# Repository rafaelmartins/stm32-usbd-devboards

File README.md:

<!-- github-to-forgejo:notice:start -->
> [!IMPORTANT]
> Development has moved to [https://git.rafaelmartins.com/rafaelmartins/stm32-usbd-devboards](https://git.rafaelmartins.com/rafaelmartins/stm32-usbd-devboards). Please check [https://git.rafaelmartins.com/](https://git.rafaelmartins.com/) for details on how to contribute.
<!-- github-to-forgejo:notice:end -->

# stm32-usbd-devboards

Breadboard-friendly development boards with dedicated USB device connectivity for STM32 microcontrollers.

For documentation please visit: https://rafaelmartins.com/p/stm32-usbd-devboards/

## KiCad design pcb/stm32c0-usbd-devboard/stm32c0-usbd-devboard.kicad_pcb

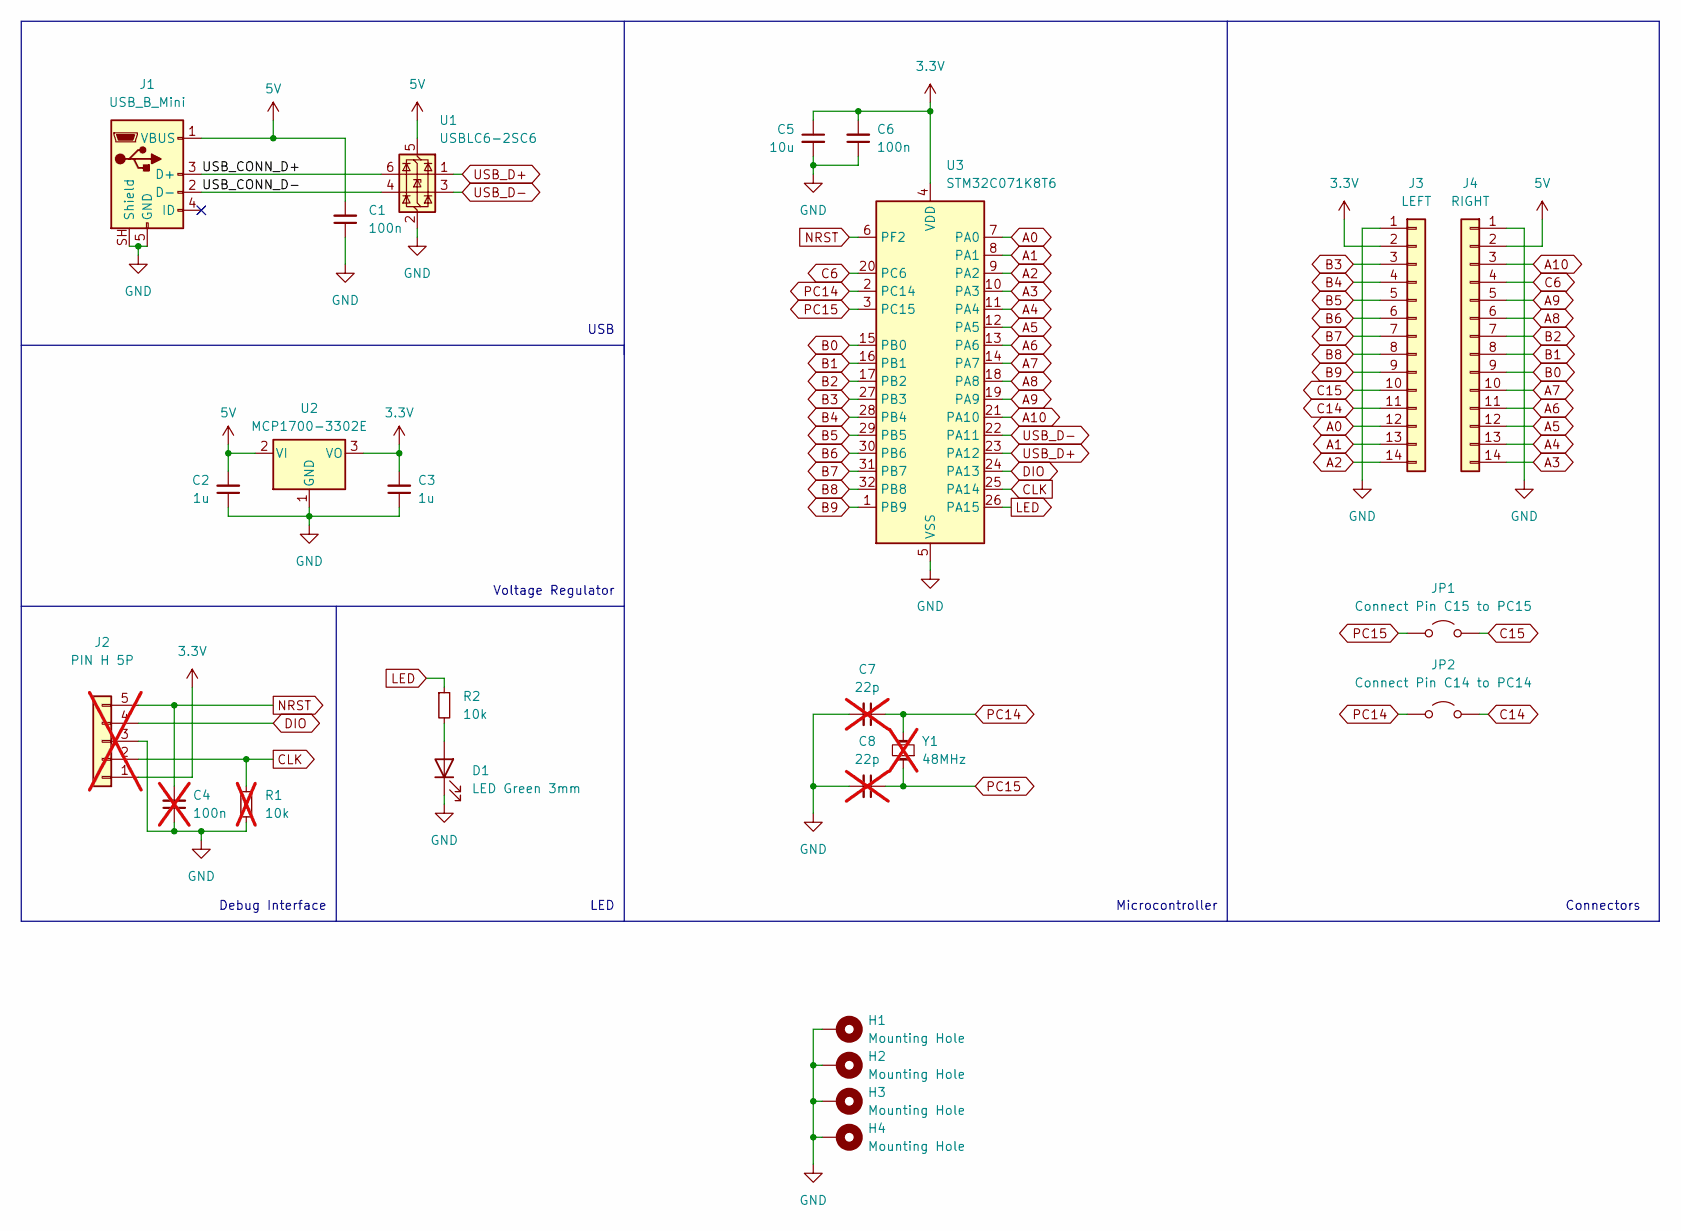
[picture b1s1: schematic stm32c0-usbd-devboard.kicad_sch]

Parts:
C1, C6: 100n; C_TDK_FA28; MPN FA28X7R1H104KNU06
C2, C3: 1u; C_TDK_FA28; MPN FA28X7R1E105KRU06
C4: 100n; C_TDK_FA28; MPN FA28X7R1H104KNU06; not fitted
C5: 10u; C_TDK_FA26; MPN FA26X7R1E106KRU06
C7, C8: 22p; C_Disc_D3.8mm_W2.6mm_P2.50mm; MPN FA28X7R1H104KNU06; not fitted
D1: LED Green 3mm; LED_D3.0mm_Horizontal_O1.27mm_Z2.0mm; MPN OVLBG4C7
H1, H2, H3, H4: Mounting Hole; MountingHole_2.2mm_M2_Pad_Via
J1: USB_B_Mini; USB_Mini-B_PTH; MPN GMSB0522132EU
J2: PIN H 5P; PinHeader_Bootloader_SWD_1x05_P2.54mm_Vertical; not fitted
J3: LEFT; PinHeader_DevBoard_Left_Connector_1x14_P2.54mm_Vertical
J4: RIGHT; PinHeader_DevBoard_Right_Connector_1x14_P2.54mm_Vertical
JP1: Connect Pin C15 to PC15; SolderJumper-2_P1.3mm_Open_TrianglePad1.0x1.5mm
JP2: Connect Pin C14 to PC14; SolderJumper-2_P1.3mm_Open_TrianglePad1.0x1.5mm
R1: 10k; R_YAGEO_MFR-25FTE52_Horizontal; MPN MFR-25FTE52-10K; not fitted
R2: 10k; R_YAGEO_MFR-25FTE52_Horizontal; MPN MFR-25FTE52-10K
U1: USBLC6-2SC6; SOT-23-6; MPN USBLC6-2SC6
U2: MCP1700-3302E; TO-92_Inline_Wide; MPN MCP1700-3302E/TO
U3: STM32C071K8T6; LQFP-32_7x7mm_P0.8mm
Y1: 48MHz; Crystal_HC49-4H_Vertical; not fitted

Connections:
3.3V: C3.2, C5.1, C6.2, J2.1, J3.2, U2.3 (VO), U3.4 (VDD)
5V: C1.2, C2.2, J1.1 (VBUS), J4.2, U1.5 (VBUS), U2.2 (VI)
/USB_CONN_D+: J1.3 (D+), U1.6 (I/O1)
/USB_CONN_D-: J1.2 (D-), U1.4 (I/O2)
A0: J3.12, U3.7 (PA0)
A1: J3.13, U3.8 (PA1)
A2: J3.14, U3.9 (PA2)
A3: J4.14, U3.10 (PA3)
A4: J4.13, U3.11 (PA4)
A5: J4.12, U3.12 (PA5)
A6: J4.11, U3.13 (PA6)
A7: J4.10, U3.14 (PA7)
A8: J4.6, U3.18 (PA8)
A9: J4.5, U3.19 (PA9)
A10: J4.3, U3.21 (PA10)
B0: J4.9, U3.15 (PB0)
B1: J4.8, U3.16 (PB1)
B2: J4.7, U3.17 (PB2)
B3: J3.3, U3.27 (PB3)
B4: J3.4, U3.28 (PB4)
B5: J3.5, U3.29 (PB5)
B6: J3.6, U3.30 (PB6)
B7: J3.7, U3.31 (PB7)
B8: J3.8, U3.32 (PB8)
B9: J3.9, U3.1 (PB9)
C6: J4.4, U3.20 (PC6)
C14: J3.11, JP2.1 (A)
C15: J3.10, JP1.1 (A)
CLK: J2.2, R1.1, U3.25 (PA14)
DIO: J2.4, U3.24 (PA13)
GND: C1.1, C2.1, C3.1, C4.1, C5.2, C6.1, C7.2, C8.2, D1.1 (K), H1.1 (1_1), H2.1 (1_1), H3.1 (1_1), H4.1 (1_1), J1.5 (GND), J1.SH (Shield), J2.3, J3.1, J4.1, R1.2, U1.2 (GND), U2.1 (GND), U3.5 (VSS)
LED: R2.1, U3.26 (PA15)
NRST: C4.2, J2.5, U3.6 (PF2)
unnamed: D1.2 (A), R2.2
PC14: C7.1, JP2.2 (B), U3.2 (PC14), Y1.2
PC15: C8.1, JP1.2 (B), U3.3 (PC15), Y1.1
USB_D+: U1.1 (I/O1), U3.23 (PA12)
USB_D-: U1.3 (I/O2), U3.22 (PA11)

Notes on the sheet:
Debug Interface
LED
Microcontroller
Connectors
Voltage Regulator
USB

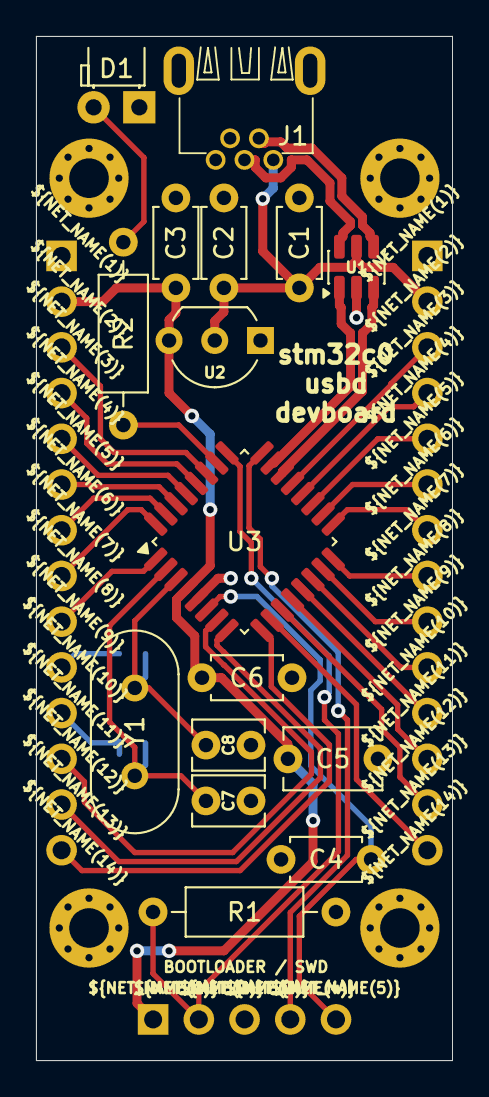
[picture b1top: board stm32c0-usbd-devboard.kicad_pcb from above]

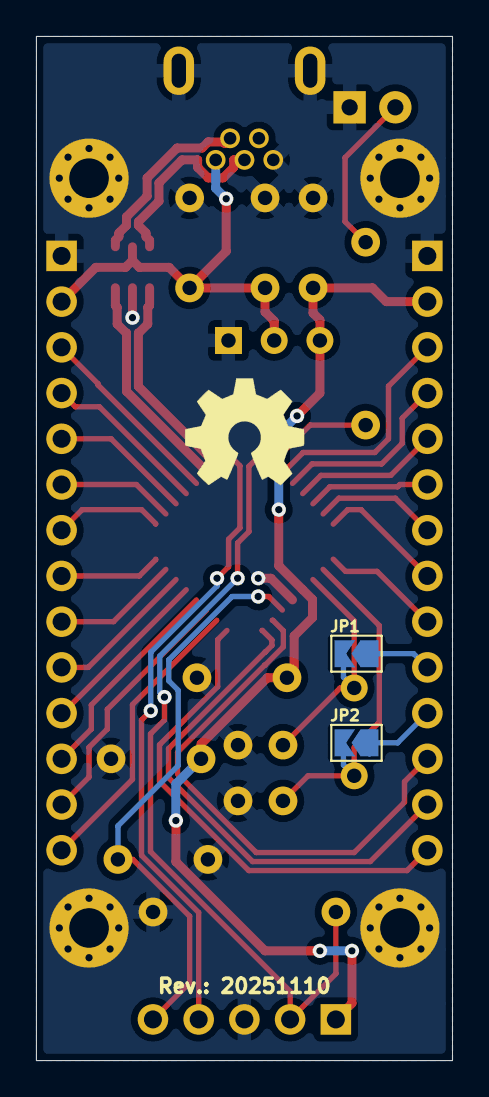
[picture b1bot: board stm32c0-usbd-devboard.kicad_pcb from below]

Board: 2 copper layers, 23.1 x 56.9 mm, 25 parts (4 on the bottom side), 38 nets.

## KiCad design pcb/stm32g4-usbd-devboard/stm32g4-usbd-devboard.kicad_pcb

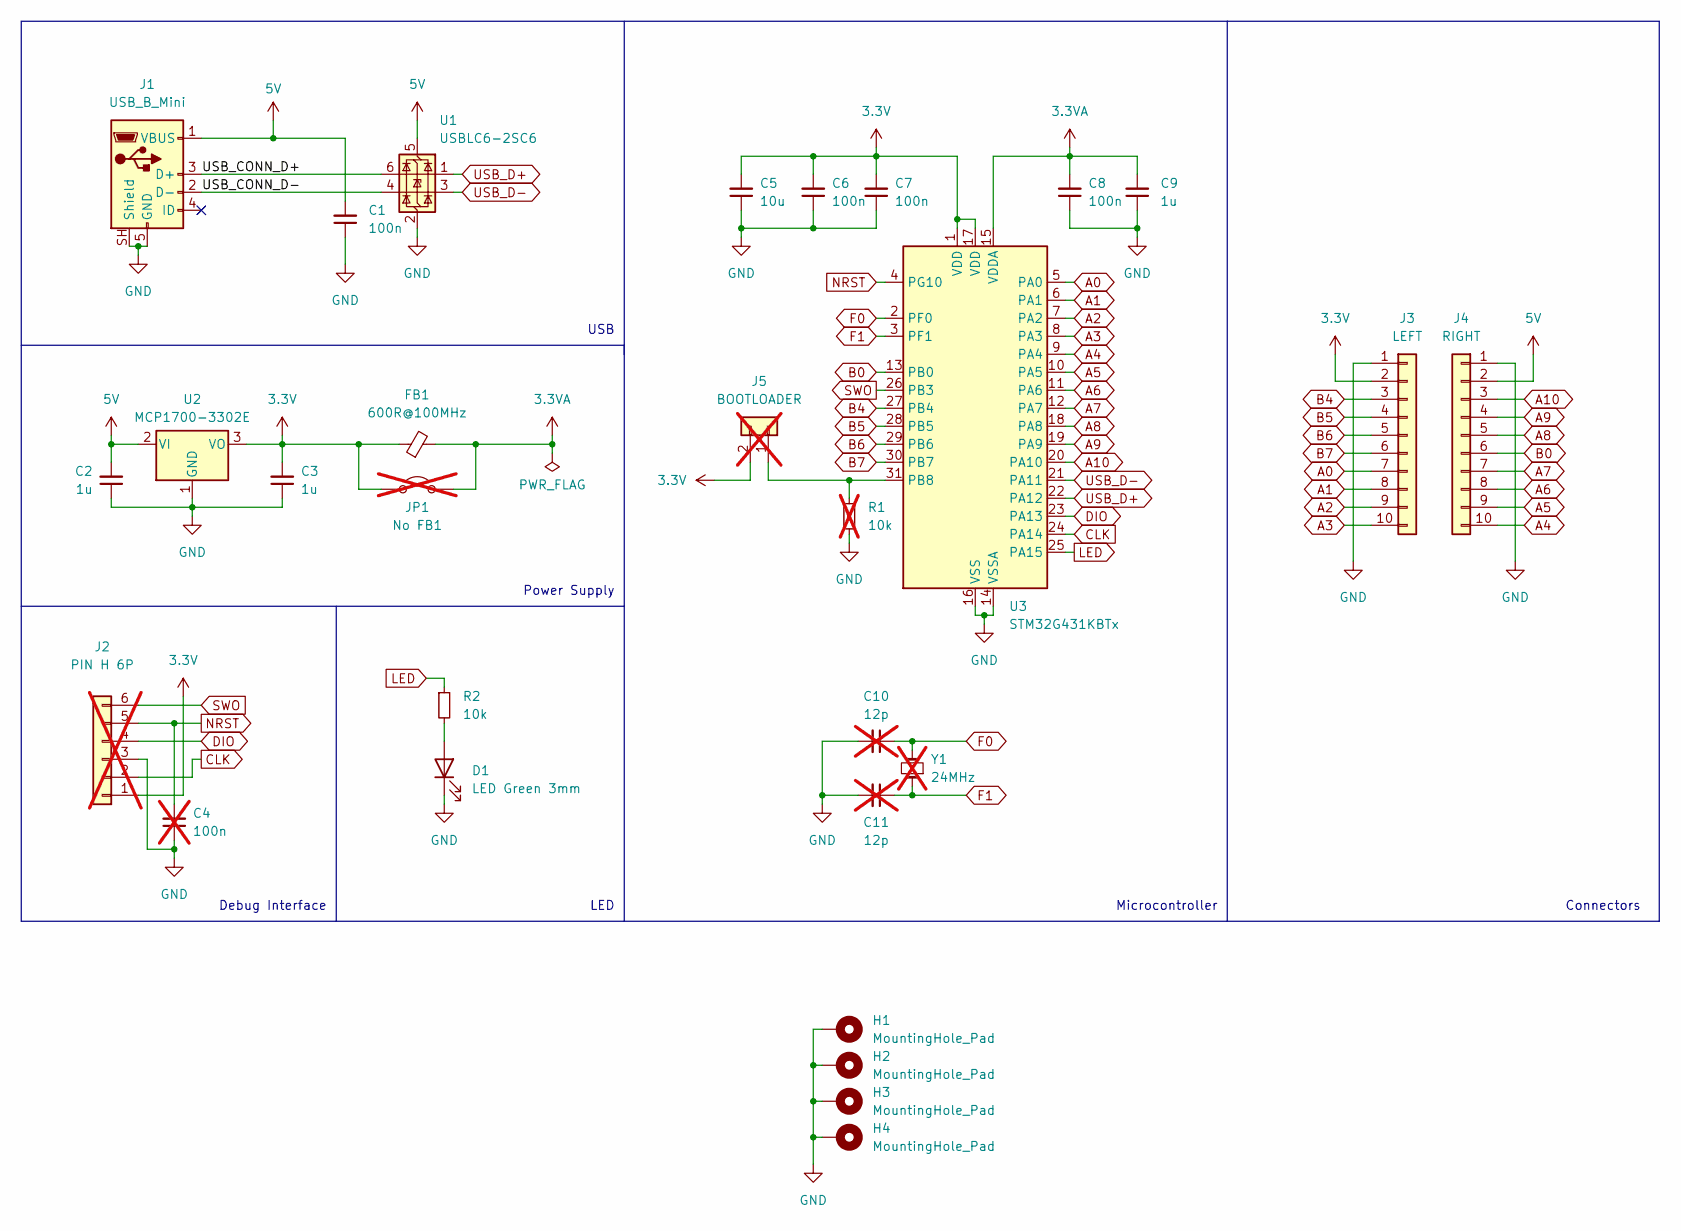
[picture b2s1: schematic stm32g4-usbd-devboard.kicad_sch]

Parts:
C1, C6, C7, C8: 100n; C_TDK_FA28; MPN FA28X7R1H104KNU06
C2, C3: 1u; C_TDK_FA28; MPN FA28X7R1E105KRU06
C4: 100n; C_TDK_FA28; MPN FA28X7R1H104KNU06; not fitted
C5: 10u; C_TDK_FA26; MPN FA26X7R1E106KRU06
C9: 1u; C_TDK_FA28; MPN FA28X7R1H104KNU06
C10, C11: 12p; C_Disc_D3.8mm_W2.6mm_P2.50mm; MPN FA28X7R1E105KRU06; not fitted
D1: LED Green 3mm; LED_D3.0mm_Horizontal_O1.27mm_Z2.0mm; MPN OVLBG4C7
FB1: 600R@100MHz; L_0603_1608Metric_Pad1.05x0.95mm_HandSolder
H1, H2, H3, H4: MountingHole_Pad; MountingHole_2.2mm_M2_Pad_Via
J1: USB_B_Mini; USB_Mini-B_PTH; MPN GMSB0522132EU
J2: PIN H 6P; PinHeader_SWD_1x06_P2.54mm_Horizontal; not fitted
J3: LEFT; PinHeader_DevBoard_Left_Connector_1x10_P2.54mm_Vertical
J4: RIGHT; PinHeader_DevBoard_Right_Connector_1x10_P2.54mm_Vertical
J5: BOOTLOADER; PinHeader_Bootloader_1x02_P2.54mm_Horizontal; not fitted
JP1: No FB1; SolderJumper-2_P1.3mm_Open_TrianglePad1.0x1.5mm; not fitted
R1: 10k; R_YAGEO_MFR-25FTE52_Horizontal; MPN MFR-25FTE52-10K; not fitted
R2: 10k; R_YAGEO_MFR-25FTE52_Horizontal; MPN MFR-25FTE52-10K
U1: USBLC6-2SC6; SOT-23-6; MPN USBLC6-2SC6
U2: MCP1700-3302E; TO-92_Inline_Wide; MPN MCP1700-3302E/TO
U3: STM32G431KBTx; LQFP-32_7x7mm_P0.8mm
Y1: 24MHz; Crystal_HC49-4H_Vertical; not fitted

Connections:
3.3V: C3.2, C5.2, C6.2, C7.2, FB1.1, J2.1, J3.2, J5.2, JP1.2 (B), U2.3 (VO), U3.1 (VDD), U3.17 (VDD)
3.3VA: C8.2, C9.2, FB1.2, JP1.1 (A), U3.15 (VDDA)
5V: C1.2, C2.2, J1.1 (VBUS), J4.2, U1.5 (VBUS), U2.2 (VI)
/USB_CONN_D+: J1.3 (D+), U1.6 (I/O1)
/USB_CONN_D-: J1.2 (D-), U1.4 (I/O2)
A0: J3.7, U3.5 (PA0)
A1: J3.8, U3.6 (PA1)
A2: J3.9, U3.7 (PA2)
A3: J3.10, U3.8 (PA3)
A4: J4.10, U3.9 (PA4)
A5: J4.9, U3.10 (PA5)
A6: J4.8, U3.11 (PA6)
A7: J4.7, U3.12 (PA7)
A8: J4.5, U3.18 (PA8)
A9: J4.4, U3.19 (PA9)
A10: J4.3, U3.20 (PA10)
B0: J4.6, U3.13 (PB0)
B4: J3.3, U3.27 (PB4)
B5: J3.4, U3.28 (PB5)
B6: J3.5, U3.29 (PB6)
B7: J3.6, U3.30 (PB7)
CLK: J2.2, U3.24 (PA14)
DIO: J2.4, U3.23 (PA13)
F0: C10.1, U3.2 (PF0), Y1.2
F1: C11.1, U3.3 (PF1), Y1.1
GND: C1.1, C2.1, C3.1, C4.1, C5.1, C6.1, C7.1, C8.1, C9.1, C10.2, C11.2, D1.1 (K), H1.1 (1_1), H2.1 (1_1), H3.1 (1_1), H4.1 (1_1), J1.5 (GND), J1.SH (Shield), J2.3, J3.1, J4.1, R1.2, U1.2 (GND), U2.1 (GND), U3.14 (VSSA), U3.16 (VSS), U3.32 (VSS)
LED: R2.1, U3.25 (PA15)
NRST: C4.2, J2.5, U3.4 (PG10)
unnamed: D1.2 (A), R2.2
unnamed: J5.1, R1.1, U3.31 (PB8)
SWO: J2.6, U3.26 (PB3)
USB_D+: U1.1 (I/O1), U3.22 (PA12)
USB_D-: U1.3 (I/O2), U3.21 (PA11)

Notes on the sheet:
Debug Interface
LED
Microcontroller
Connectors
Power Supply
USB

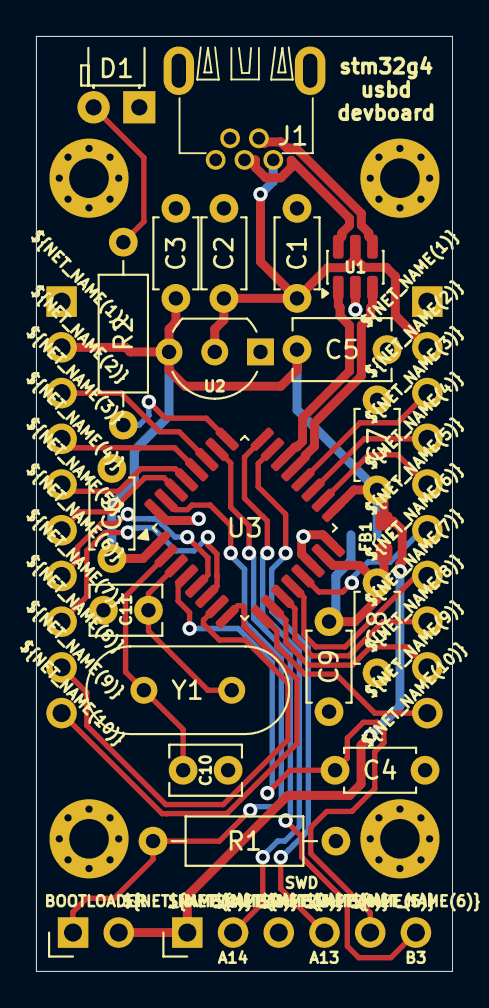
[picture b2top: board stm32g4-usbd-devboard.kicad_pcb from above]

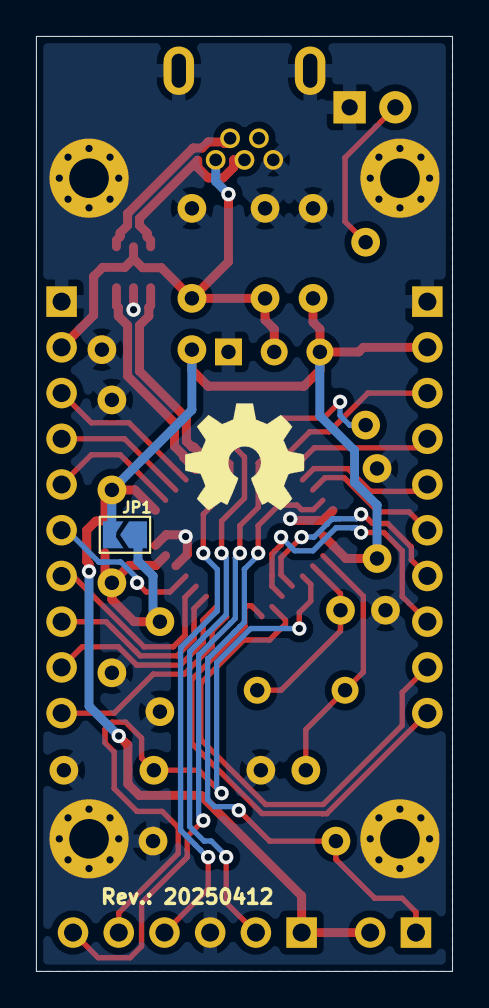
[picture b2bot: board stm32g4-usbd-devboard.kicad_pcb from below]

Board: 2 copper layers, 23.1 x 51.9 mm, 29 parts (3 on the bottom side), 33 nets.

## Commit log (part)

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2025-04-12 pcb: import sources as they were last produced
2025-04-12 pcb: consolidate kicad libraries
2025-04-13 pcb: *: new revision: 20250412
2025-04-17 build: add github actions workflow to build and deploy pcb assets
2025-04-17 build: use relative paths for index page
2025-04-17 readme: added some documentation
2025-04-18 build: generate montage with front and back 3d render
2025-04-19 readme: split legacy revisions to a dedicated page
2025-04-19 symbols: added kicad symbols
2025-04-19 legacy-revisions: typo
2025-04-20 readme: add a description to each variant
2025-06-12 pcb: f0: fix crystal capacitor values
    trivial fix not affecting any physical layers, not bumping revision.
2025-07-20 pcb: f0: g4: minor schematic symbol fixes
    trivial fix not affecting any board files, not bumping revision.
2025-07-20 pcb: f0: g4: delete schematic pdfs
    they are now generated on demand by github actions
2025-07-20 build: minor fixes
2025-08-07 build: use kicad 9.0 nightly for ci
2025-08-13 build: fix 3d rendering of dnp parts
2025-12-07 rework pcb asset build pipeline
2026-02-09 pcb: c0: initial revision 20251110
2026-02-09 pcb: c0: added pcb asset build config
2026-02-10 docs: started new documentation website
2026-02-10 docs: minor fixes
2026-02-10 docs: fix index image sizes
2026-02-10 docs: harmonize style with other projects
2026-02-21 build: rename action rafaelmartins/website/{kicad,hardware}
2026-02-22 Revert "build: rename action rafaelmartins/website/{kicad,hardware}"
    This reverts commit cf9ebdc07a408e897589e579c1503bb26a4f33f2.
2026-02-22 pcb: update asset gen config files
2026-02-27 pcb: c0: fix crystal frequency
    no physical layer changes, no revision bump.
2026-02-27 docs: update
2026-02-27 docs: f0: minor rewording
2026-02-28 docs: remove custom styles
2026-03-01 symbols: add stm32c0-usbd-devboard symbol
2026-03-02 docs: mention kicad symbols
2026-05-06 docs: add stm32c0 crystal warning
2026-05-06 pcb: symbols: upgrade footprints and symbols to kicad 10
2026-05-06 pcb: f0: upgrade to kicad 10
2026-05-06 pcb: g4: upgrade to kicad 10
2026-05-06 pcb: c0: upgrade to kicad 10

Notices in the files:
pcb/stm32c0-usbd-devboard/stm32c0-usbd-devboard.kicad_pcb:
Released under CERN Open Hardware Licence Version 2 - Strongly Reciprocal
